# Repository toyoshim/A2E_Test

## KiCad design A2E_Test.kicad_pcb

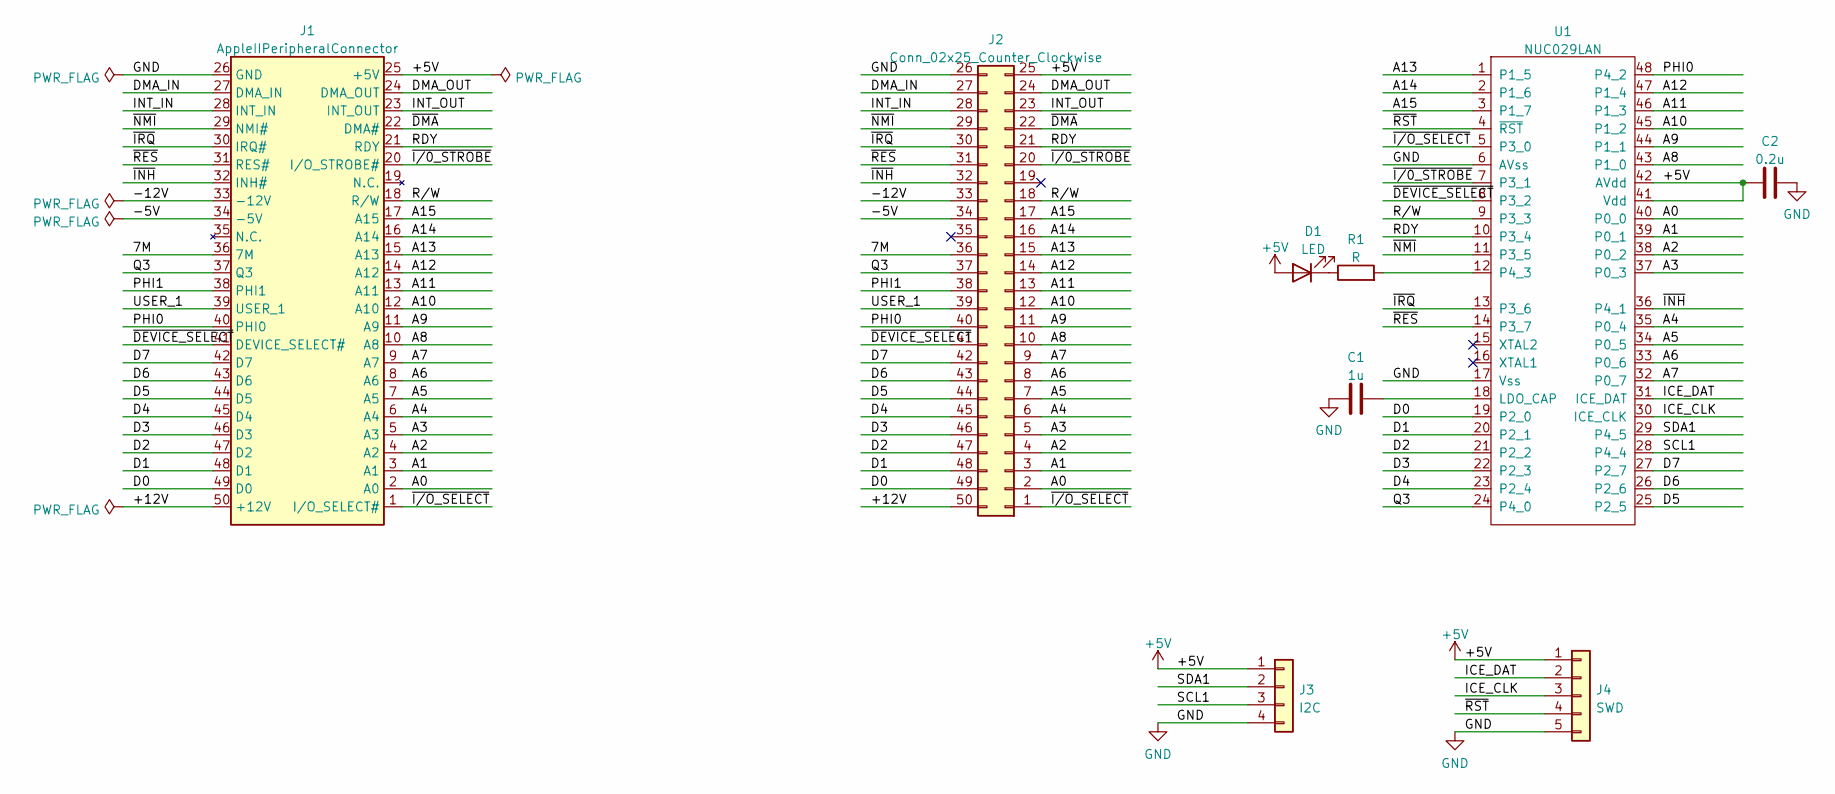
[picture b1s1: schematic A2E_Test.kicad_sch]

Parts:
C1: 1u; C_0603_1608Metric_Pad1.08x0.95mm_HandSolder
C2: 0.2u; C_0603_1608Metric_Pad1.08x0.95mm_HandSolder
D1: LED; LED_0603_1608Metric_Pad1.05x0.95mm_HandSolder
J1: AppleIIPeripheralConnector; Connector_Edge_02x25_AppleII
J2: Conn_02x25_Counter_Clockwise; PinHeader_2x25_P2.54mm_Vertical_Clockwise
J3: I2C; PinHeader_1x04_P2.54mm_Vertical
J4: SWD; PinHeader_1x05_P2.54mm_Vertical
R1: R; R_0603_1608Metric_Pad0.98x0.95mm_HandSolder
U1: NUC029LAN; LQFP-48_7x7mm_P0.5mm

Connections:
+5V: C2.1, D1.2 (A), J1.25 (+5V), J2.25, J3.1, J4.1, U1.41 (Vdd), U1.42 (AVdd)
/7M: J1.36 (7M), J2.36
/+12V: J1.50 (+12V), J2.50
/-5V: J1.34 (-5V), J2.34
/-12V: J1.33 (-12V), J2.33
/A0: J1.2 (A0), J2.2, U1.40 (P0_0)
/A1: J1.3 (A1), J2.3, U1.39 (P0_1)
/A2: J1.4 (A2), J2.4, U1.38 (P0_2)
/A3: J1.5 (A3), J2.5, U1.37 (P0_3)
/A4: J1.6 (A4), J2.6, U1.35 (P0_4)
/A5: J1.7 (A5), J2.7, U1.34 (P0_5)
/A6: J1.8 (A6), J2.8, U1.33 (P0_6)
/A7: J1.9 (A7), J2.9, U1.32 (P0_7)
/A8: J1.10 (A8), J2.10, U1.43 (P1_0)
/A9: J1.11 (A9), J2.11, U1.44 (P1_1)
/A10: J1.12 (A10), J2.12, U1.45 (P1_2)
/A11: J1.13 (A11), J2.13, U1.46 (P1_3)
/A12: J1.14 (A12), J2.14, U1.47 (P1_4)
/A13: J1.15 (A13), J2.15, U1.1 (P1_5)
/A14: J1.16 (A14), J2.16, U1.2 (P1_6)
/A15: J1.17 (A15), J2.17, U1.3 (P1_7)
/D0: J1.49 (D0), J2.49, U1.19 (P2_0)
/D1: J1.48 (D1), J2.48, U1.20 (P2_1)
/D2: J1.47 (D2), J2.47, U1.21 (P2_2)
/D3: J1.46 (D3), J2.46, U1.22 (P2_3)
/D4: J1.45 (D4), J2.45, U1.23 (P2_4)
/D5: J1.44 (D5), J2.44, U1.25 (P2_5)
/D6: J1.43 (D6), J2.43, U1.26 (P2_6)
/D7: J1.42 (D7), J2.42, U1.27 (P2_7)
/DMA_IN: J1.27 (DMA_IN), J2.27
/DMA_OUT: J1.24 (DMA_OUT), J2.24
/ICE_CLK: J4.3, U1.30 (ICE_CLK)
/ICE_DAT: J4.2, U1.31 (ICE_DAT)
/INT_IN: J1.28 (INT_IN), J2.28
/INT_OUT: J1.23 (INT_OUT), J2.23
/PHI0: J1.40 (PHI0), J2.40, U1.48 (P4_2)
/PHI1: J1.38 (PHI1), J2.38
/Q3: J1.37 (Q3), J2.37, U1.24 (P4_0)
/RDY: J1.21 (RDY), J2.21, U1.10 (P3_4)
/R/W: J1.18 (R/W), J2.18, U1.9 (P3_3)
/SCL1: J3.3, U1.28 (P4_4)
/SDA1: J3.2, U1.29 (P4_5)
/USER_1: J1.39 (USER_1), J2.39
/~DEVICE_SELECT: J1.41 (DEVICE_SELECT#), J2.41, U1.8 (P3_2)
/~DMA: J1.22 (DMA#), J2.22
/~INH: J1.32 (INH#), J2.32, U1.36 (P4_1)
/~IRQ: J1.30 (IRQ#), J2.30, U1.13 (P3_6)
/~I/0_STROBE: J1.20 (I/O_STROBE#), J2.20, U1.7 (P3_1)
/~I/O_SELECT: J1.1 (I/O_SELECT#), J2.1, U1.5 (P3_0)
/~NMI: J1.29 (NMI#), J2.29, U1.11 (P3_5)
/~RES: J1.31 (RES#), J2.31, U1.14 (P3_7)
/~RST: J4.4, U1.4 (~RST)
GND: C1.1, C2.2, J1.26 (GND), J2.26, J3.4, J4.5, U1.6 (AVss), U1.17 (Vss)
unnamed: C1.2, U1.18 (LDO_CAP)
unnamed: D1.1 (K), R1.1
unnamed: R1.2, U1.12 (P4_3)

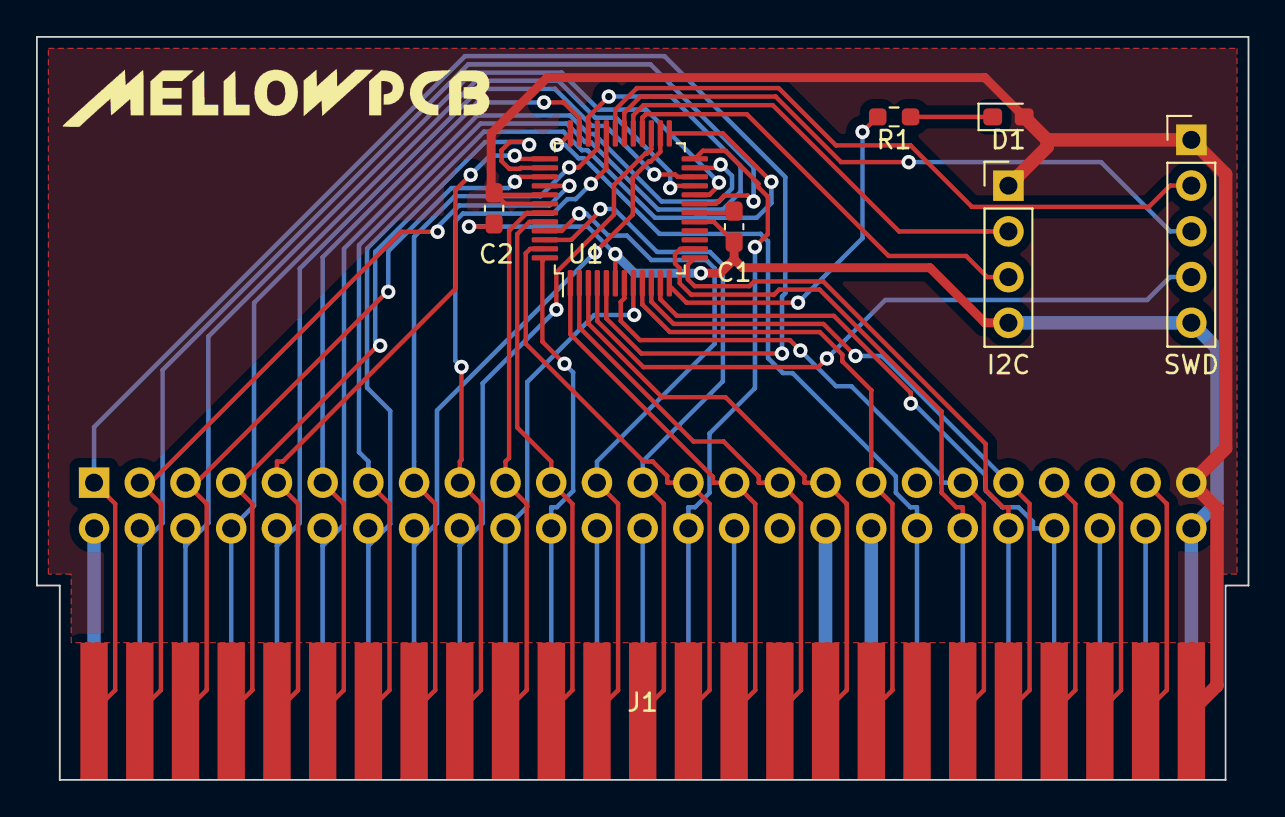
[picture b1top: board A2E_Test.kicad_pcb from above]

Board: 2 copper layers, 67.3 x 41.3 mm, 10 parts (1 on the bottom side), 56 nets.

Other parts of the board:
G1: LOGO; MellowPCB

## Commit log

2022-10-09 rename
